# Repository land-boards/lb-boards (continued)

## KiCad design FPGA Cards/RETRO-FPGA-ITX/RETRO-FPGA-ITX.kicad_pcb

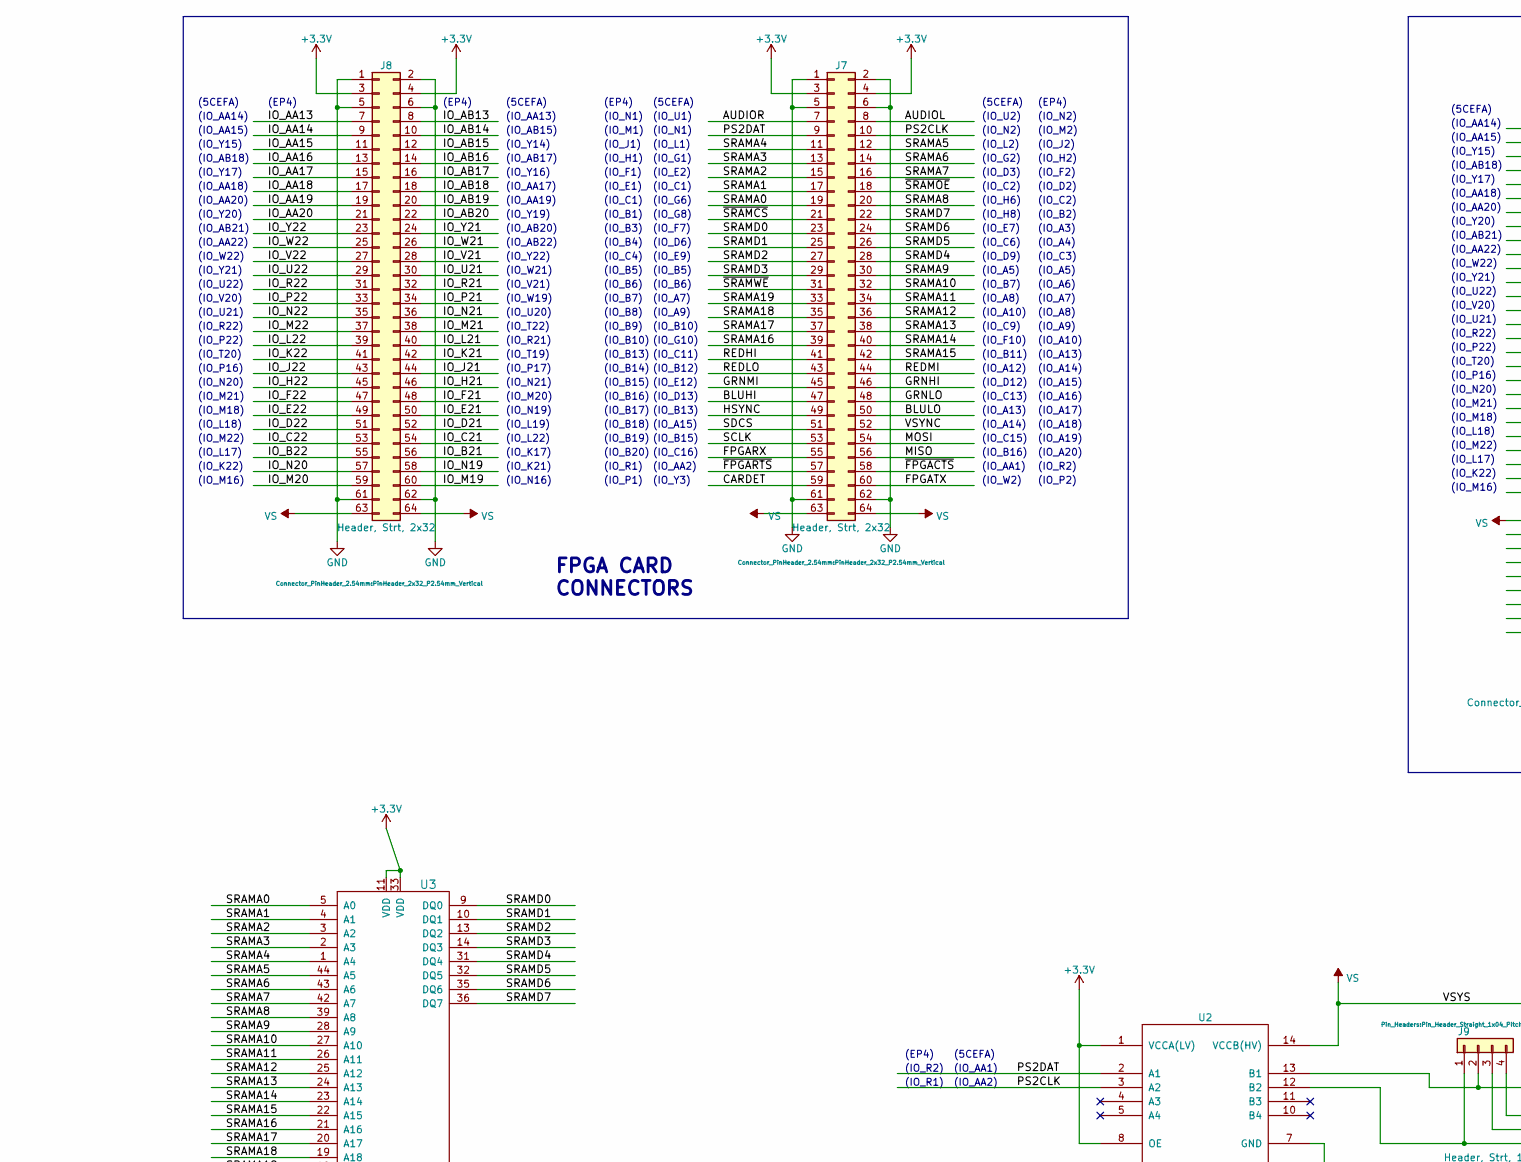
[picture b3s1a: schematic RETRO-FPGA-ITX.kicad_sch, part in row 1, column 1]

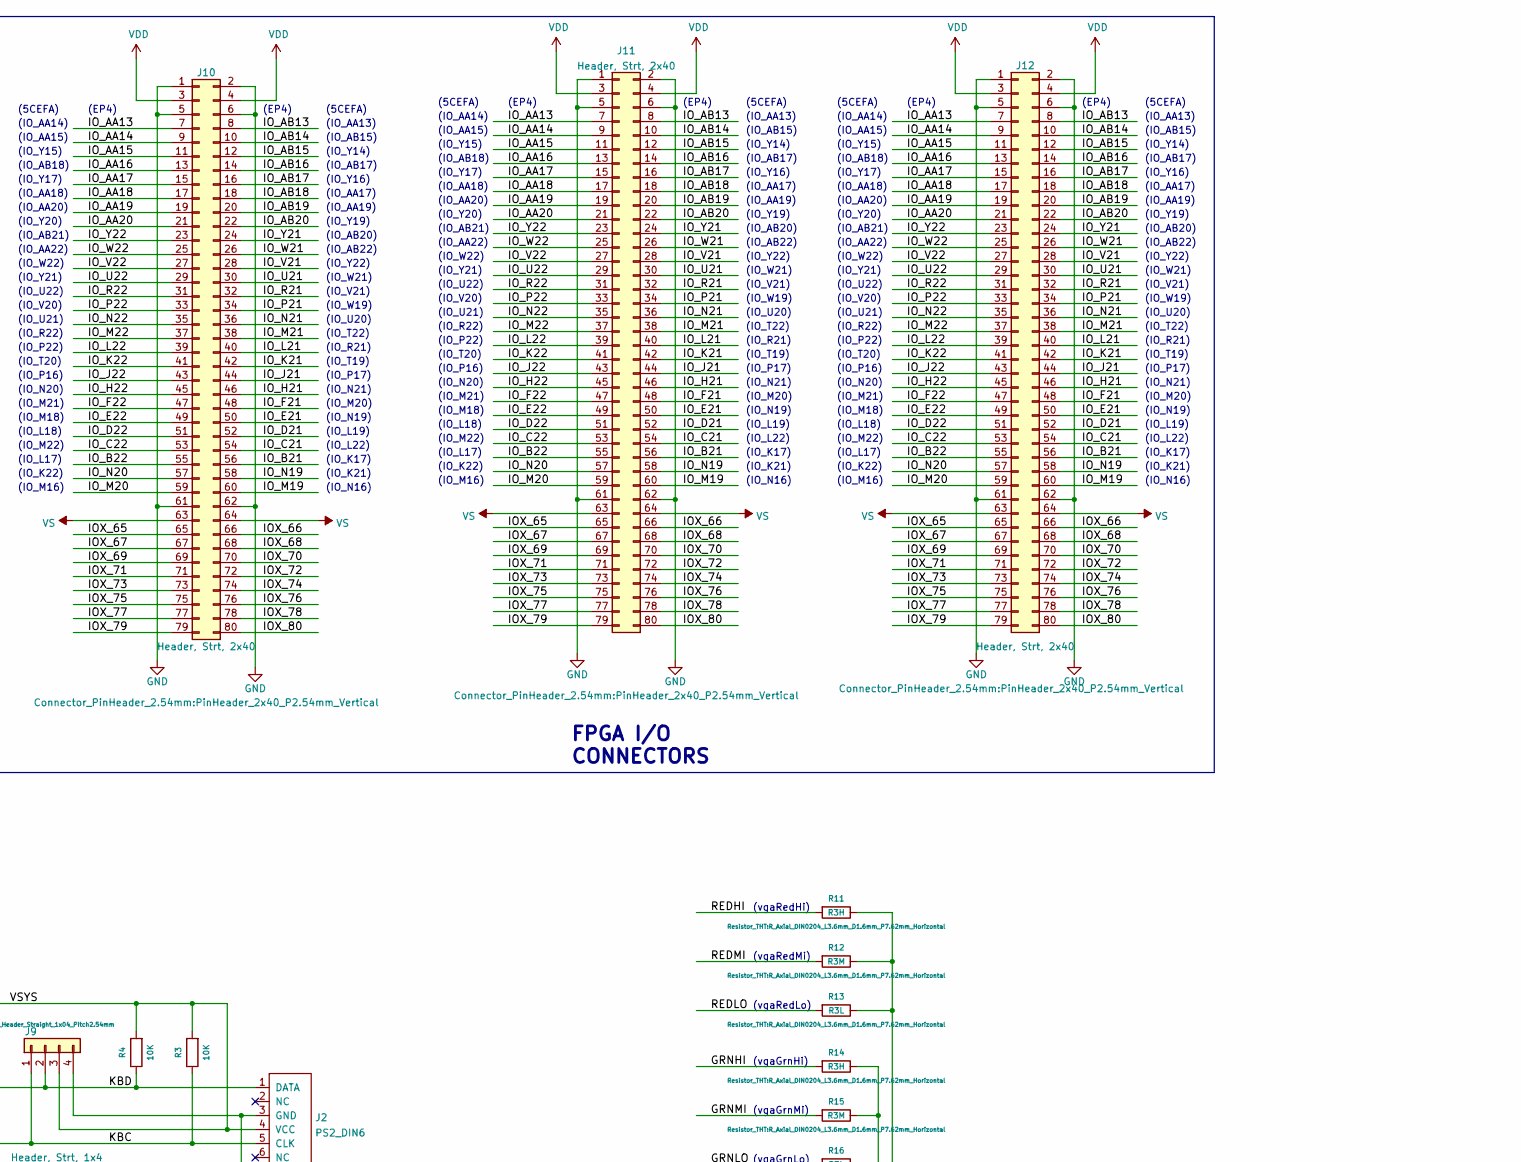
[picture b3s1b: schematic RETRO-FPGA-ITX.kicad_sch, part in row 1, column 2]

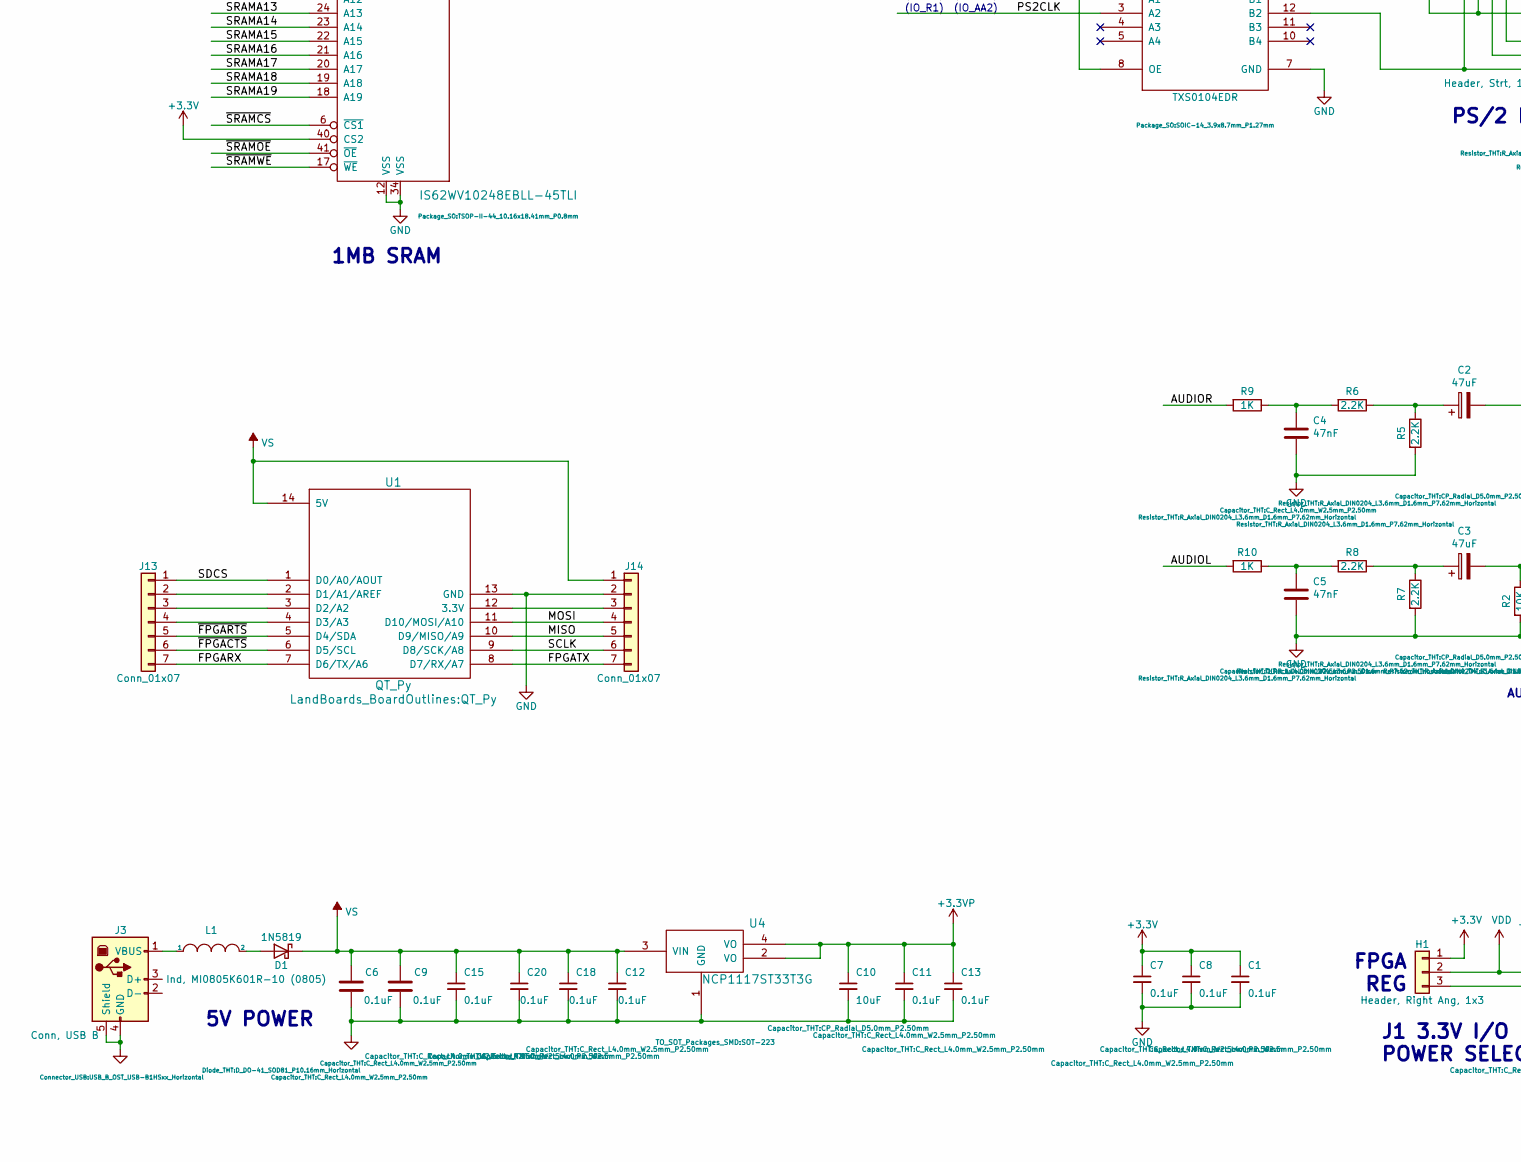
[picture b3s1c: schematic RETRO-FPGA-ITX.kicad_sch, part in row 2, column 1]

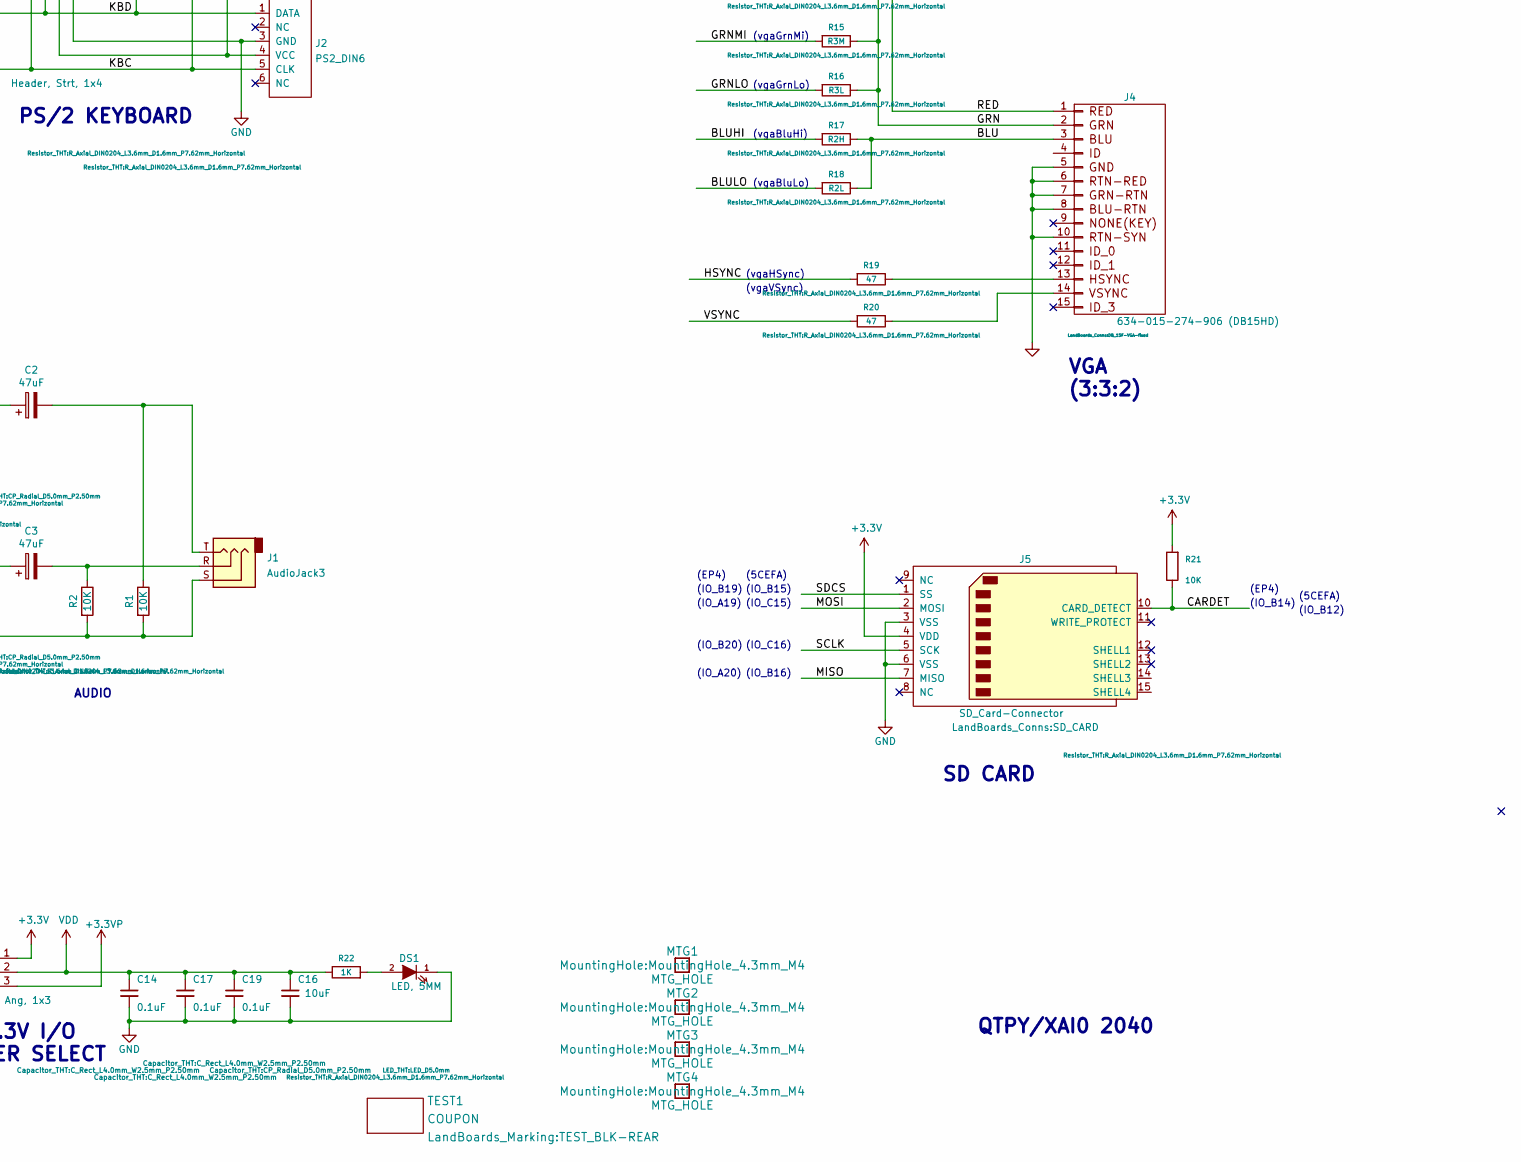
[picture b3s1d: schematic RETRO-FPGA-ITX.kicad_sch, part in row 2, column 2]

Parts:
C1, C6, C7, C8, C9, C11, C12, C13, C14, C15, C17, C18, C19, C20: 0.1uF; C_Rect_L4.0mm_W2.5mm_P2.50mm
C2, C3: 47uF; CP_Radial_D5.0mm_P2.50mm
C4, C5: 47nF; C_Rect_L4.0mm_W2.5mm_P2.50mm
C10, C16: 10uF; CP_Radial_D5.0mm_P2.50mm
D1: 1N5819; D_DO-41_SOD81_P10.16mm_Horizontal
DS1: LED, 5MM; LED_D5.0mm
H1: Header, Right Ang, 1x3; PinHeader_1x03_P2.54mm_Horizontal
J1: AudioJack3; Jack_3.5mm_CUI_SJ1-3523N_Horizontal
J2: PS2_DIN6; Connector_Mini-DIN_Female_6Pin_2rows
J3: Conn, USB B; USB_B_OST_USB-B1HSxx_Horizontal
J4: 634-015-274-906 (DB15HD); DB_15F-VGA-fixed
J5: SD_Card-Connector; SD_CARD
J7, J8: Header, Strt, 2x32; PinHeader_2x32_P2.54mm_Vertical
J9: Header, Strt, 1x4; Pin_Header_Straight_1x04_Pitch2.54mm
J10, J11, J12: Header, Strt, 2x40; PinHeader_2x40_P2.54mm_Vertical
J13, J14: Conn_01x07; PinHeader_1x07_P2.54mm_Vertical
L1: Ind, MI0805K601R-10 (0805); L_0805_2012Metric_Pad1.15x1.40mm_HandSolder
MTG1, MTG2, MTG3, MTG4: MTG_HOLE; MountingHole_4.3mm_M4
R1, R2, R3, R4, R21: 10K; R_Axial_DIN0204_L3.6mm_D1.6mm_P7.62mm_Horizontal
R5, R6, R7, R8: 2.2K; R_Axial_DIN0204_L3.6mm_D1.6mm_P7.62mm_Horizontal
R9, R10, R22: 1K; R_Axial_DIN0204_L3.6mm_D1.6mm_P7.62mm_Horizontal
R11, R14: R3H; R_Axial_DIN0204_L3.6mm_D1.6mm_P7.62mm_Horizontal
R12, R15: R3M; R_Axial_DIN0204_L3.6mm_D1.6mm_P7.62mm_Horizontal
R13, R16: R3L; R_Axial_DIN0204_L3.6mm_D1.6mm_P7.62mm_Horizontal
R17: R2H; R_Axial_DIN0204_L3.6mm_D1.6mm_P7.62mm_Horizontal
R18: R2L; R_Axial_DIN0204_L3.6mm_D1.6mm_P7.62mm_Horizontal
R19, R20: 47; R_Axial_DIN0204_L3.6mm_D1.6mm_P7.62mm_Horizontal
TEST1: COUPON; TEST_BLK-REAR
U1: QT_Py
U2: TXS0104EDR; SOIC-14_3.9x8.7mm_P1.27mm
U3: IS62WV10248EBLL-45TLI; TSOP-II-44_10.16x18.41mm_P0.8mm
U4: NCP1117ST33T3G; SOT-223

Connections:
+3.3VP: C10.1, C11.1, C13.1, H1.3, U4.2 (VO), U4.4 (VO)
+3V3: C1.1, C7.1, C8.1, H1.1, J5.4 (VDD), J7.3, J7.4, J8.3, J8.4, R21.2, U2.1 (VCCA(LV)), U2.8 (OE), U3.11 (VDD), U3.33 (VDD), U3.40 (CS2)
/AUDIOL: J7.8, R10.2
/AUDIOR: J7.7, R9.2
/BLU: J4.3, R17.1, R18.1
/BLUHI: J7.47, R17.2
/BLULO: J7.50, R18.2
/CARDET: J5.10 (CARD_DETECT), J7.59, R21.1
/FPGARX: J7.55, J13.7, U1.7 (D6/TX/A6)
/FPGATX: J7.60, J14.7, U1.8 (D7/RX/A7)
/GRN: J4.2, R14.1, R15.1, R16.1
/GRNHI: J7.46, R14.2
/GRNLO: J7.48, R16.2
/GRNMI: J7.45, R15.2
/HSYNC: J7.49, R19.2
/IOX_65: J10.65, J11.65, J12.65
/IOX_66: J10.66, J11.66, J12.66
/IOX_67: J10.67, J11.67, J12.67
/IOX_68: J10.68, J11.68, J12.68
/IOX_69: J10.69, J11.69, J12.69
/IOX_70: J10.70, J11.70, J12.70
/IOX_71: J10.71, J11.71, J12.71
/IOX_72: J10.72, J11.72, J12.72
/IOX_73: J10.73, J11.73, J12.73
/IOX_74: J10.74, J11.74, J12.74
/IOX_75: J10.75, J11.75, J12.75
/IOX_76: J10.76, J11.76, J12.76
/IOX_77: J10.77, J11.77, J12.77
/IOX_78: J10.78, J11.78, J12.78
/IOX_79: J10.79, J11.79, J12.79
/IOX_80: J10.80, J11.80, J12.80
/IO_AA13: J8.7, J10.7, J11.7, J12.7
/IO_AA14: J8.9, J10.9, J11.9, J12.9
/IO_AA15: J8.11, J10.11, J11.11, J12.11
/IO_AA16: J8.13, J10.13, J11.13, J12.13
/IO_AA17: J8.15, J10.15, J11.15, J12.15
/IO_AA18: J8.17, J10.17, J11.17, J12.17
/IO_AA19: J8.19, J10.19, J11.19, J12.19
/IO_AA20: J8.21, J10.21, J11.21, J12.21
/IO_AB13: J8.8, J10.8, J11.8, J12.8
/IO_AB14: J8.10, J10.10, J11.10, J12.10
/IO_AB15: J8.12, J10.12, J11.12, J12.12
/IO_AB16: J8.14, J10.14, J11.14, J12.14
/IO_AB17: J8.16, J10.16, J11.16, J12.16
/IO_AB18: J8.18, J10.18, J11.18, J12.18
/IO_AB19: J8.20, J10.20, J11.20, J12.20
/IO_AB20: J8.22, J10.22, J11.22, J12.22
/IO_B21: J8.56, J10.56, J11.56, J12.56
/IO_B22: J8.55, J10.55, J11.55, J12.55
/IO_C21: J8.54, J10.54, J11.54, J12.54
/IO_C22: J8.53, J10.53, J11.53, J12.53
/IO_D21: J8.52, J10.52, J11.52, J12.52
/IO_D22: J8.51, J10.51, J11.51, J12.51
/IO_E21: J8.50, J10.50, J11.50, J12.50
/IO_E22: J8.49, J10.49, J11.49, J12.49
/IO_F21: J8.48, J10.48, J11.48, J12.48
/IO_F22: J8.47, J10.47, J11.47, J12.47
/IO_H21: J8.46, J10.46, J11.46, J12.46
/IO_H22: J8.45, J10.45, J11.45, J12.45
/IO_J21: J8.44, J10.44, J11.44, J12.44
/IO_J22: J8.43, J10.43, J11.43, J12.43
/IO_K21: J8.42, J10.42, J11.42, J12.42
/IO_K22: J8.41, J10.41, J11.41, J12.41
/IO_L21: J8.40, J10.40, J11.40, J12.40
/IO_L22: J8.39, J10.39, J11.39, J12.39
/IO_M19: J8.60, J10.60, J11.60, J12.60
/IO_M20: J8.59, J10.59, J11.59, J12.59
/IO_M21: J8.38, J10.38, J11.38, J12.38
/IO_M22: J8.37, J10.37, J11.37, J12.37
/IO_N19: J8.58, J10.58, J11.58, J12.58
/IO_N20: J8.57, J10.57, J11.57, J12.57
/IO_N21: J8.36, J10.36, J11.36, J12.36
/IO_N22: J8.35, J10.35, J11.35, J12.35
/IO_P21: J8.34, J10.34, J11.34, J12.34
/IO_P22: J8.33, J10.33, J11.33, J12.33
/IO_R21: J8.32, J10.32, J11.32, J12.32
/IO_R22: J8.31, J10.31, J11.31, J12.31
/IO_U21: J8.30, J10.30, J11.30, J12.30
/IO_U22: J8.29, J10.29, J11.29, J12.29
/IO_V21: J8.28, J10.28, J11.28, J12.28
/IO_V22: J8.27, J10.27, J11.27, J12.27
/IO_W21: J8.26, J10.26, J11.26, J12.26
/IO_W22: J8.25, J10.25, J11.25, J12.25
/IO_Y21: J8.24, J10.24, J11.24, J12.24
/IO_Y22: J8.23, J10.23, J11.23, J12.23
/KBC: J2.5 (CLK), J9.1, R3.1, U2.12 (B2)
/KBD: J2.1 (DATA), J9.2, R4.1, U2.13 (B1)
/MISO: J5.7 (MISO), J7.56, J14.5, U1.10 (D9/MISO/A9)
/MOSI: J5.2 (MOSI), J7.54, J14.4, U1.11 (D10/MOSI/A10)
/PS2CLK: J7.10, U2.3 (A2)
/PS2DAT: J7.9, U2.2 (A1)
/RED: J4.1, R11.1, R12.1, R13.1
/REDHI: J7.41, R11.2
/REDLO: J7.43, R13.2
/REDMI: J7.44, R12.2
/SCLK: J5.5 (SCK), J7.53, J14.6, U1.9 (D8/SCK/A8)
/SDCS: J5.1 (SS), J7.51, J13.1, U1.1 (D0/A0/AOUT)
/SRAMA0: J7.19, U3.5 (A0)
/SRAMA1: J7.17, U3.4 (A1)
/SRAMA2: J7.15, U3.3 (A2)
/SRAMA3: J7.13, U3.2 (A3)
/SRAMA4: J7.11, U3.1 (A4)
/SRAMA5: J7.12, U3.44 (A5)
/SRAMA6: J7.14, U3.43 (A6)
/SRAMA7: J7.16, U3.42 (A7)
/SRAMA8: J7.20, U3.39 (A8)
/SRAMA9: J7.30, U3.28 (A9)
/SRAMA10: J7.32, U3.27 (A10)
/SRAMA11: J7.34, U3.26 (A11)
/SRAMA12: J7.36, U3.25 (A12)
/SRAMA13: J7.38, U3.24 (A13)
/SRAMA14: J7.40, U3.23 (A14)
/SRAMA15: J7.42, U3.22 (A15)
/SRAMA16: J7.39, U3.21 (A16)
/SRAMA17: J7.37, U3.20 (A17)
/SRAMA18: J7.35, U3.19 (A18)
/SRAMA19: J7.33, U3.18 (A19)
/SRAMD0: J7.23, U3.9 (DQ0)
/SRAMD1: J7.25, U3.10 (DQ1)
/SRAMD2: J7.27, U3.13 (DQ2)
/SRAMD3: J7.29, U3.14 (DQ3)
/SRAMD4: J7.28, U3.31 (DQ4)
/SRAMD5: J7.26, U3.32 (DQ5)
/SRAMD6: J7.24, U3.35 (DQ6)
/SRAMD7: J7.22, U3.36 (DQ7)
/VSYNC: J7.52, R20.2
/~FPGACTS: J7.58, J13.6, U1.6 (D5/SCL)
/~FPGARTS: J7.57, J13.5, U1.5 (D4/SDA)
/~SRAMCS: J7.21, U3.6 (~CS1)
/~SRAMOE: J7.18, U3.41 (~OE)
/~SRAMWE: J7.31, U3.17 (~WE)
GND: C1.2, C4.2, C5.2, C6.2, C7.2, C8.2, C9.2, C10.2, C11.2, C12.2, C13.2, C14.2, C15.2, C16.2, C17.2, C18.2, C19.2, C20.2, DS1.1 (K), J1.S, J2.3 (GND), J3.4 (GND), J3.5 (Shield), J4.5, J4.6, J4.7, J4.8, J4.10, J5.3 (VSS), J5.6 (VSS), J7.1, J7.2, J7.5, J7.6, J7.61, J7.62, J8.1, J8.2, J8.5, J8.6, J8.61, J8.62, J9.4, J10.1, J10.2, J10.5, J10.6, J10.61, J10.62, J11.1, J11.2, J11.5, J11.6, J11.61, J11.62, J12.1, J12.2, J12.5, J12.6, J12.61, J12.62, J14.2, R1.2, R2.2, R5.2, R7.2, U1.13 (GND), U2.7 (GND), U3.12 (VSS), U3.34 (VSS), U4.1 (GND)
unnamed: C2.1, R5.1, R6.1
unnamed: C2.2, J1.T, R1.1
unnamed: C3.1, R7.1, R8.1
unnamed: C3.2, J1.R, R2.1
unnamed: C4.1, R6.2, R9.1
unnamed: C5.1, R8.2, R10.1
unnamed: D1.2 (A), L1.2
unnamed: DS1.2 (A), R22.2
unnamed: J3.1 (VBUS), L1.1
unnamed: J4.13, R19.1
unnamed: J4.14, R20.1
unnamed: J13.2, U1.2 (D1/A1/AREF)
unnamed: J13.3, U1.3 (D2/A2)
unnamed: J13.4, U1.4 (D3/A3)
unnamed: J14.3, U1.12 (3.3V)
VDD: C14.1, C16.1, C17.1, C19.1, H1.2, J10.3, J10.4, J11.3, J11.4, J12.3, J12.4, R22.1
VS: C6.1, C9.1, C12.1, C15.1, C18.1, C20.1, D1.1 (K), J2.4 (VCC), J7.63, J7.64, J8.63, J8.64, J9.3, J10.63, J10.64, J11.63, J11.64, J12.63, J12.64, J14.1, R3.2, R4.2, U1.14 (5V), U2.14 (VCCB(HV)), U4.3 (VIN)

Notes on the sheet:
(IO_B5)
(IO_B18)
(IO_AA20)
(IO_B10)
(IO_K22)
(EP4)
(IO_Y19)
(IO_J1)
(IO_R2)
(IO_M18)
(IO_B17)
(IO_K21)
(IO_C2)
(IO_AA2)
(IO_A13)
(5CEFA)
1MB SRAM
(IO_AA1)
(IO_T22)
(vgaVSync)
(IO_A5)
(IO_Y15)
(IO_N20)
(IO_N21)
(vgaRedLo)
(IO_N1)
(IO_L18)
(IO_L17)
(vgaBluLo)
(IO_AA17)
(IO_N19)
(IO_H8)
(vgaHSync)
(IO_AA13)
(IO_P17)
(IO_W22)
(IO_C15)
(IO_B7)
5V POWER
(IO_A14)

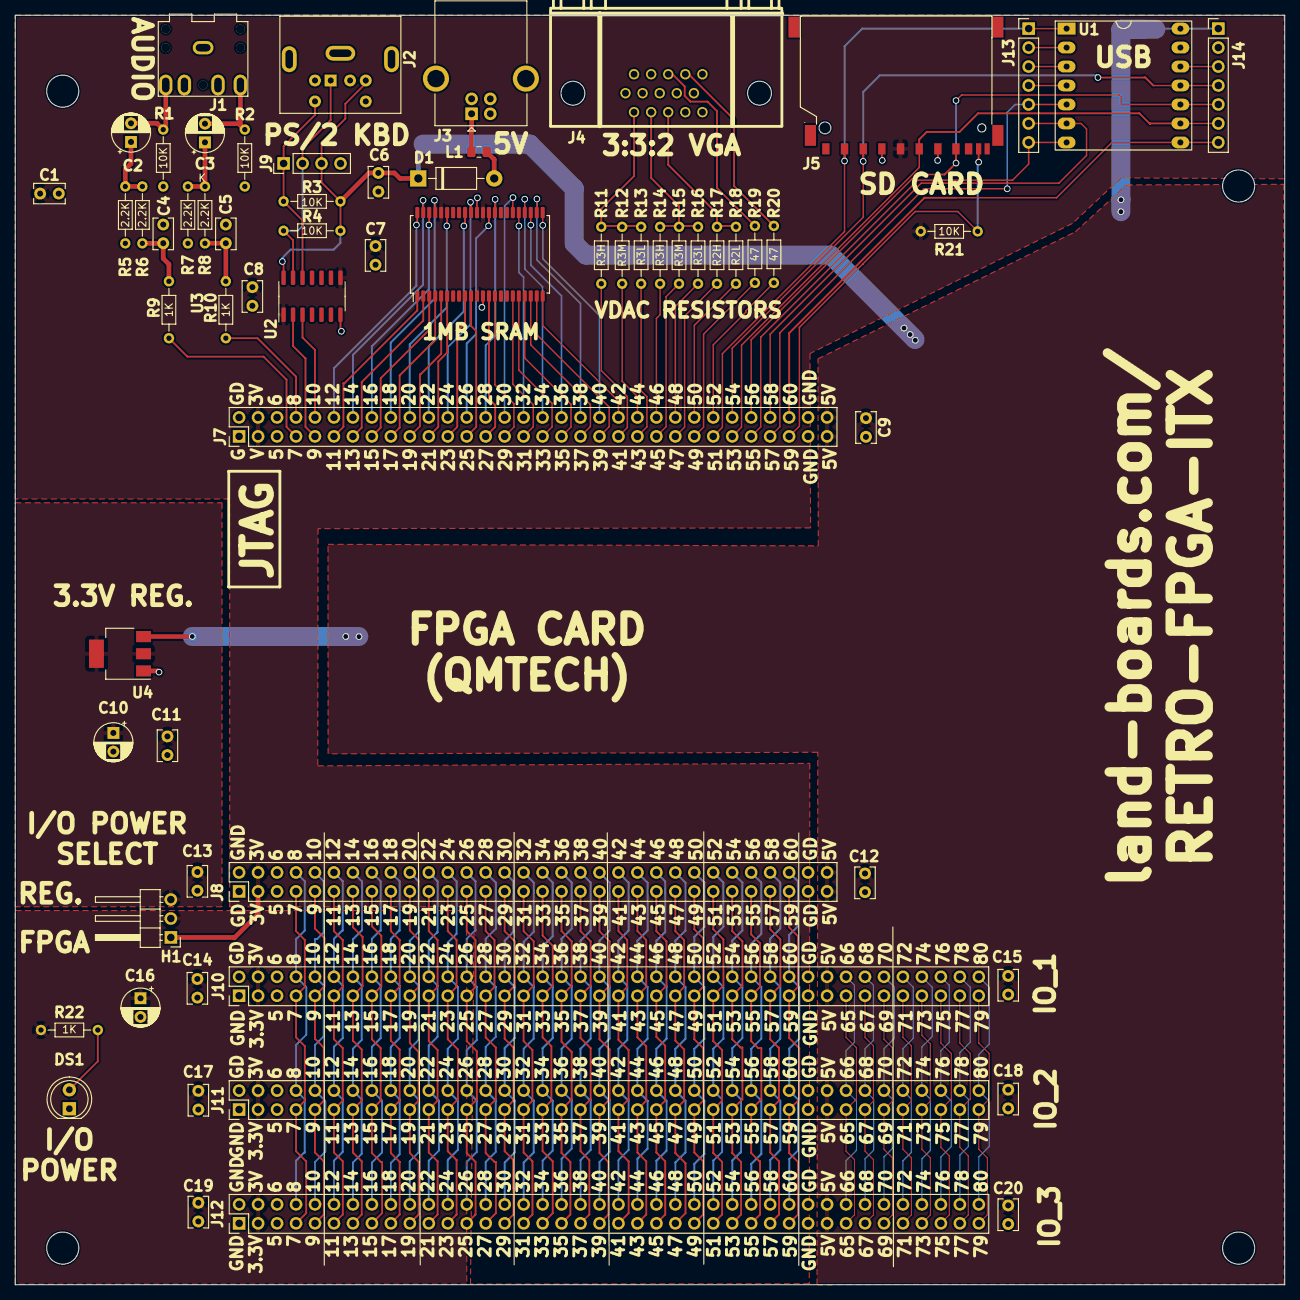
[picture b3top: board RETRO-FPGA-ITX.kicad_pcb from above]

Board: 2 copper layers, 170.0 x 170.0 mm, 68 parts (0 on the bottom side), 149 nets.

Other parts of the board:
TEST: COUPON; TEST_BLK-REAR

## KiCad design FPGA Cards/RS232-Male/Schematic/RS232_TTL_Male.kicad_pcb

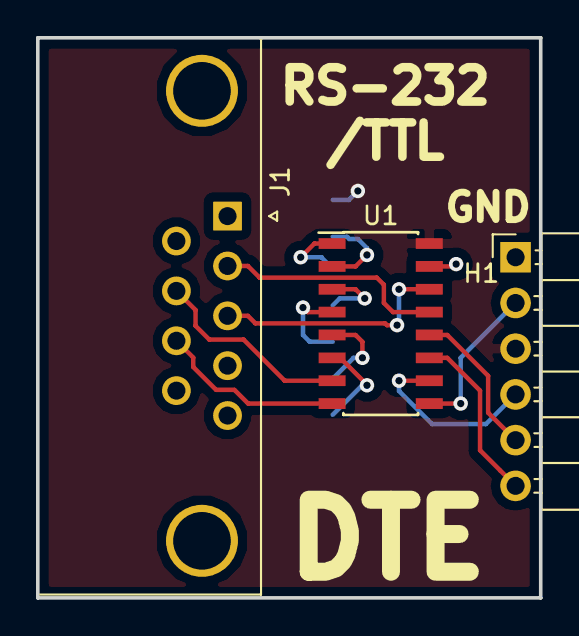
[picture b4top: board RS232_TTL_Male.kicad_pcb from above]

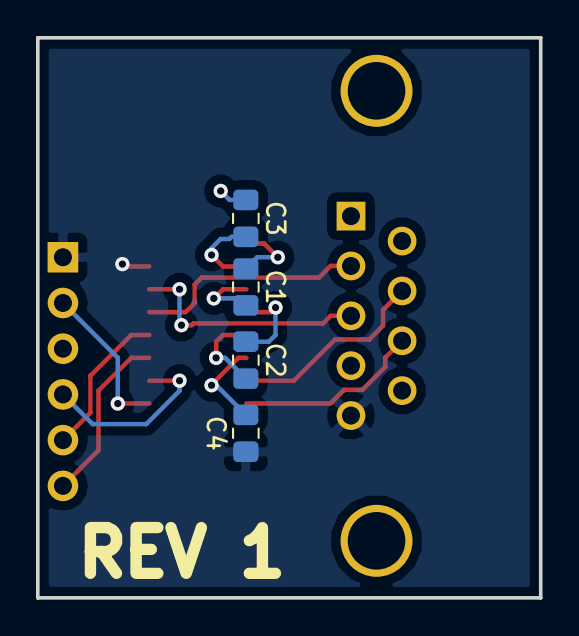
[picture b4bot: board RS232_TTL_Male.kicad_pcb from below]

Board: 2 copper layers, 27.9 x 31.1 mm, 7 parts (4 on the bottom side), 16 nets.

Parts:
C1, C2, C3, C4: 0.1uF; C_0805_2012Metric_Pad1.15x1.40mm_HandSolder
H1: FTDI-Slave; PinHeader_1x06_P2.54mm_Horizontal
J1: DB9_Male_MountingHoles; DSUB-9_Male_Horizontal_P2.77x2.84mm_EdgePinOffset7.70mm_Hou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
U1: ICL3232; SOIC-16_3.9x9.9mm_P1.27mm

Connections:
/VCC: C3.1, H1.3, U1.16
GND: C4.1, H1.1, J1.5, U1.15
unnamed: C1.1, U1.1
unnamed: C1.2, U1.3
unnamed: C2.1, U1.4
unnamed: C2.2, U1.5
unnamed: C3.2, U1.2
unnamed: C4.2, U1.6
unnamed: H1.2, U1.9
unnamed: H1.4, U1.10
unnamed: H1.5, U1.12
unnamed: H1.6, U1.11
unnamed: J1.2, U1.13
unnamed: J1.3, U1.14
unnamed: J1.7, U1.7
unnamed: J1.8, U1.8

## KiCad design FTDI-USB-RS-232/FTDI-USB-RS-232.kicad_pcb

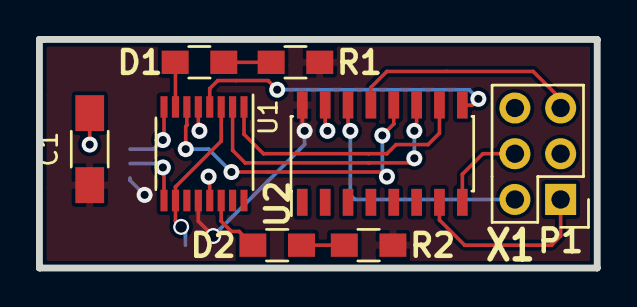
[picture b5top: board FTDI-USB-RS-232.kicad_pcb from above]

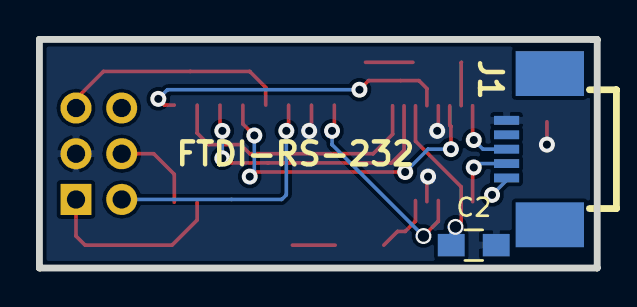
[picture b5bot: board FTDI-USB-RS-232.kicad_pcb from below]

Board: 2 copper layers, 31.0 x 12.7 mm, 10 parts (2 on the bottom side), 17 nets.

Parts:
C1: 10uF; C_1206_HandSoldering
C2: 0.1uF; C_0805_HandSoldering
D1, D2: LED; R_0805_HandSoldering
J1: USB-B; J1
P1: CONN_01X05; Pin_Header_Straight_2x03
R1, R2: 270; R_0805_HandSoldering
U1: FT230XS; SSOP-16_3.9x4.9mm_Pitch0.635mm
U2: MAX3232; SOIC-16_3.9x9.9mm_Pitch1.27mm

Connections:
/+3.3V: C2.1, U1.3, U1.10
/+5V: C1.1, J1.1, R1.1, R2.1, U1.12, U2.16
/CTS: U1.6, U2.12
/DM: J1.2, U1.9
/DP: J1.3, U1.8
/PUP0: D1.1, R1.2
/PUP1: D2.1, R2.2
/RTS: U1.2, U2.11
/RX: U1.4, U2.9
/RXLED*: D2.2, U1.14
/TX: U1.1, U2.10
/TXLED*: D1.2, U1.7
GND: C1.2, C2.2, J1.4, P1.3, U1.5, U1.13, U2.15
unnamed: P1.1, U2.7
unnamed: P1.2, U2.14
unnamed: P1.4, U2.8
unnamed: P1.5, U2.13

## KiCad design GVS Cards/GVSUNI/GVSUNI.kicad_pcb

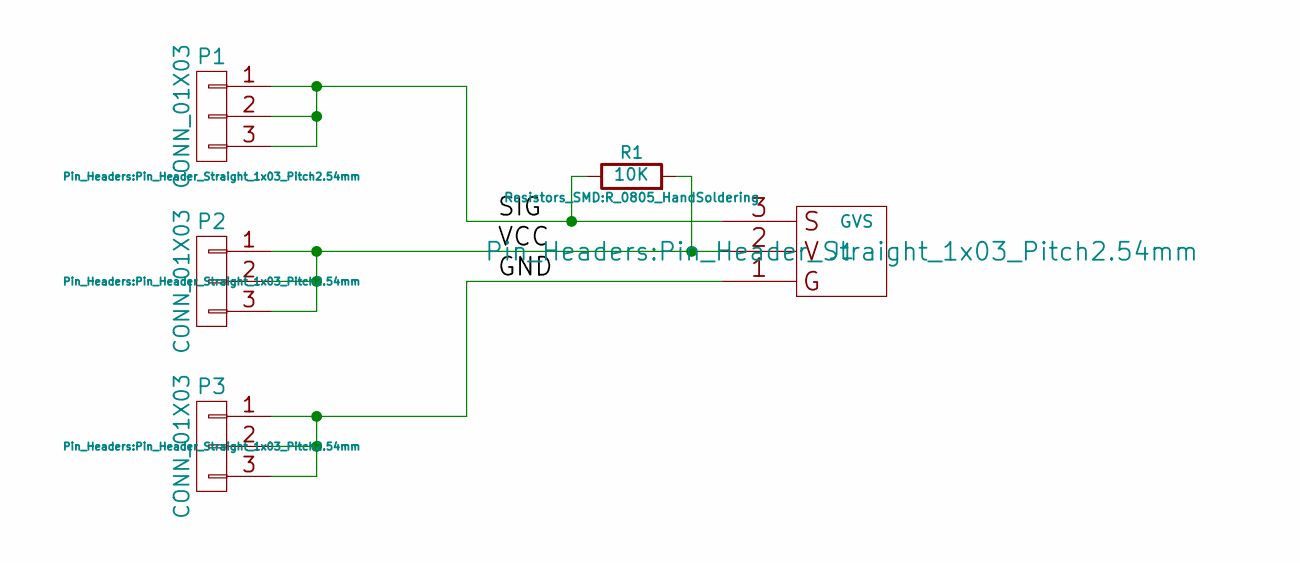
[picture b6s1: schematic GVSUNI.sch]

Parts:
J1: GVS; Pin_Header_Straight_1x03_Pitch2.54mm
P1, P2, P3: CONN_01X03; Pin_Header_Straight_1x03_Pitch2.54mm
R1: 10K; R_0805_HandSoldering

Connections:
/GND: J1.1 (G), P3.1, P3.2, P3.3
/SIG: J1.3 (S), P1.1, P1.2, P1.3, R1.1
/VCC: J1.2 (V), P2.1, P2.2, P2.3, R1.2

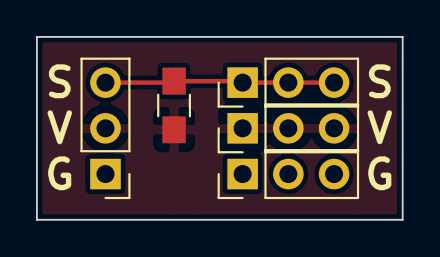
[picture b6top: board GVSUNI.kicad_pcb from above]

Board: 2 copper layers, 20.3 x 10.2 mm, 5 parts (0 on the bottom side), 3 nets.
